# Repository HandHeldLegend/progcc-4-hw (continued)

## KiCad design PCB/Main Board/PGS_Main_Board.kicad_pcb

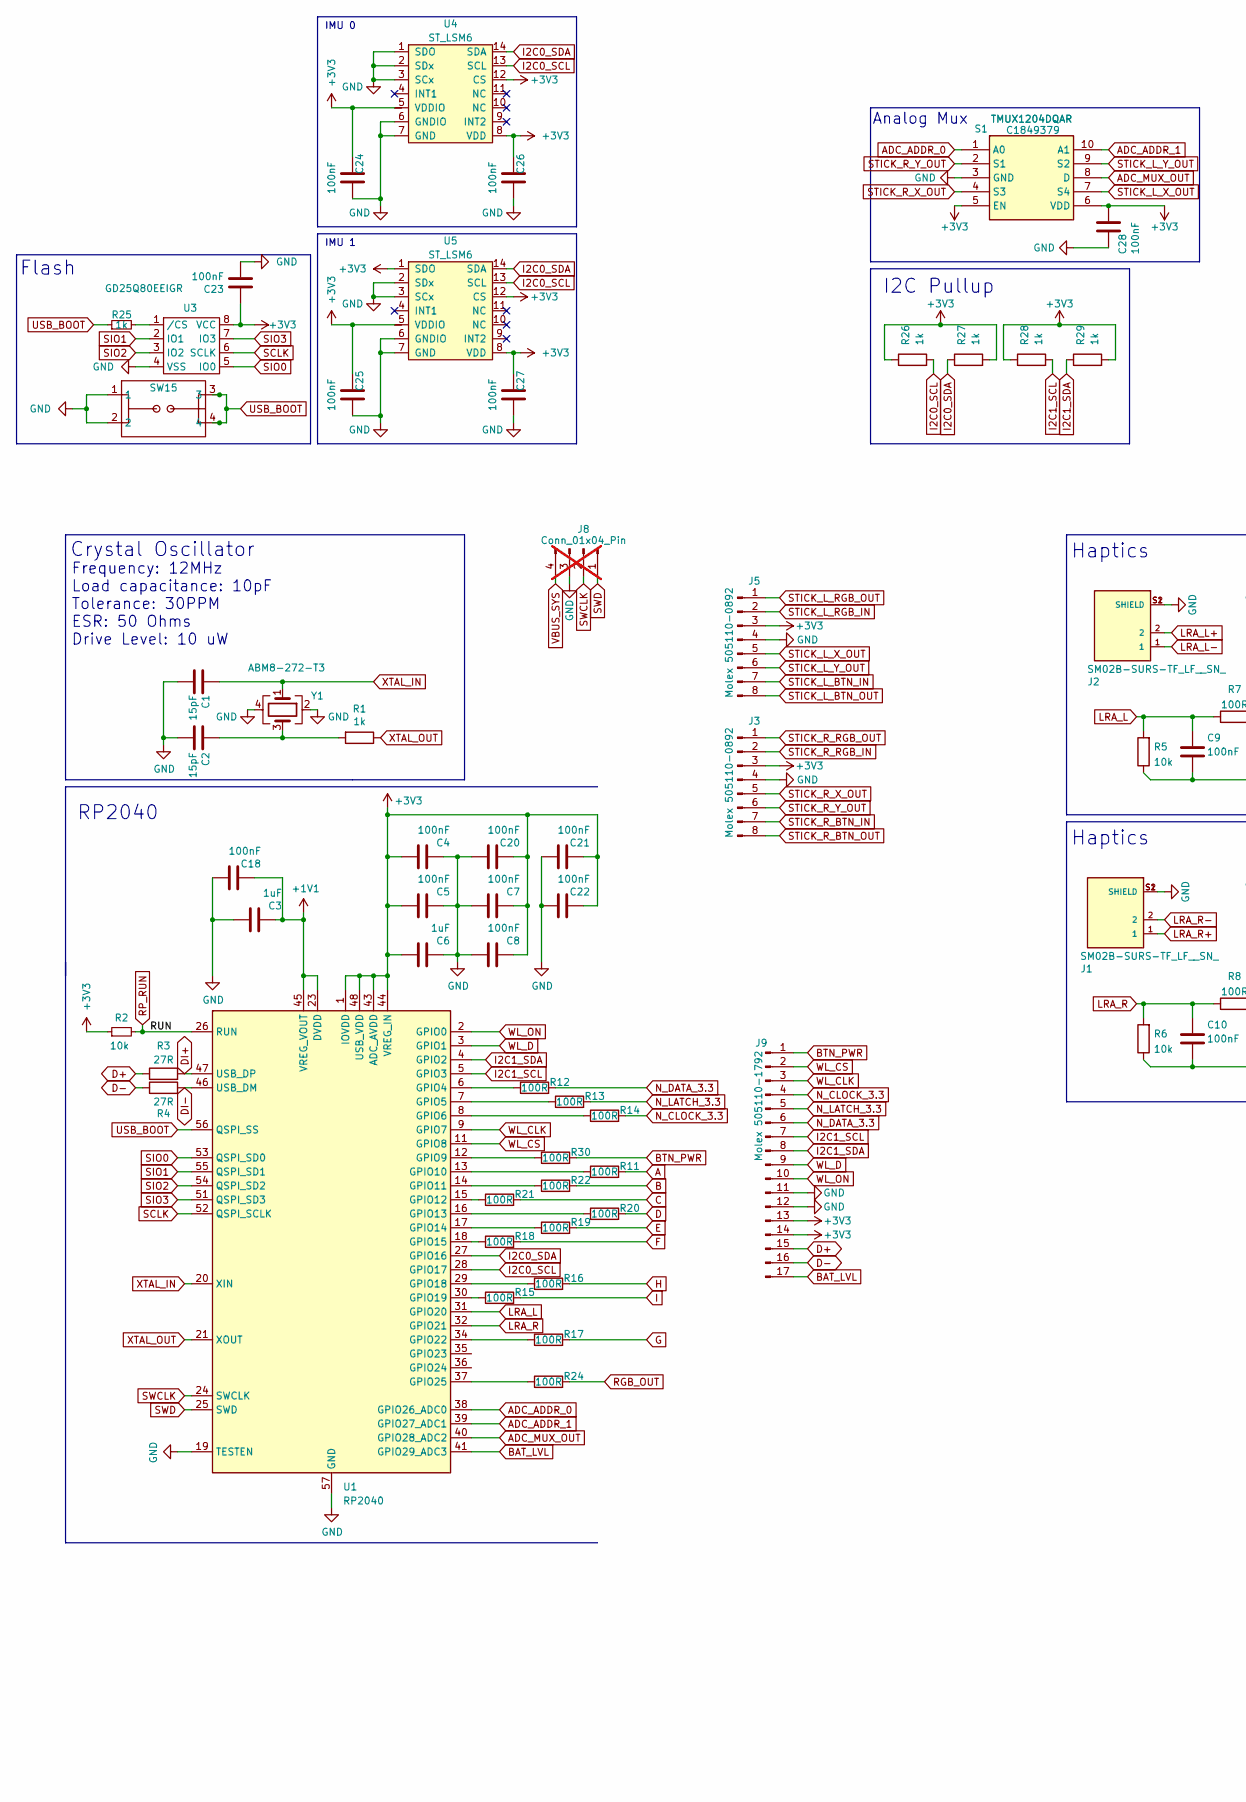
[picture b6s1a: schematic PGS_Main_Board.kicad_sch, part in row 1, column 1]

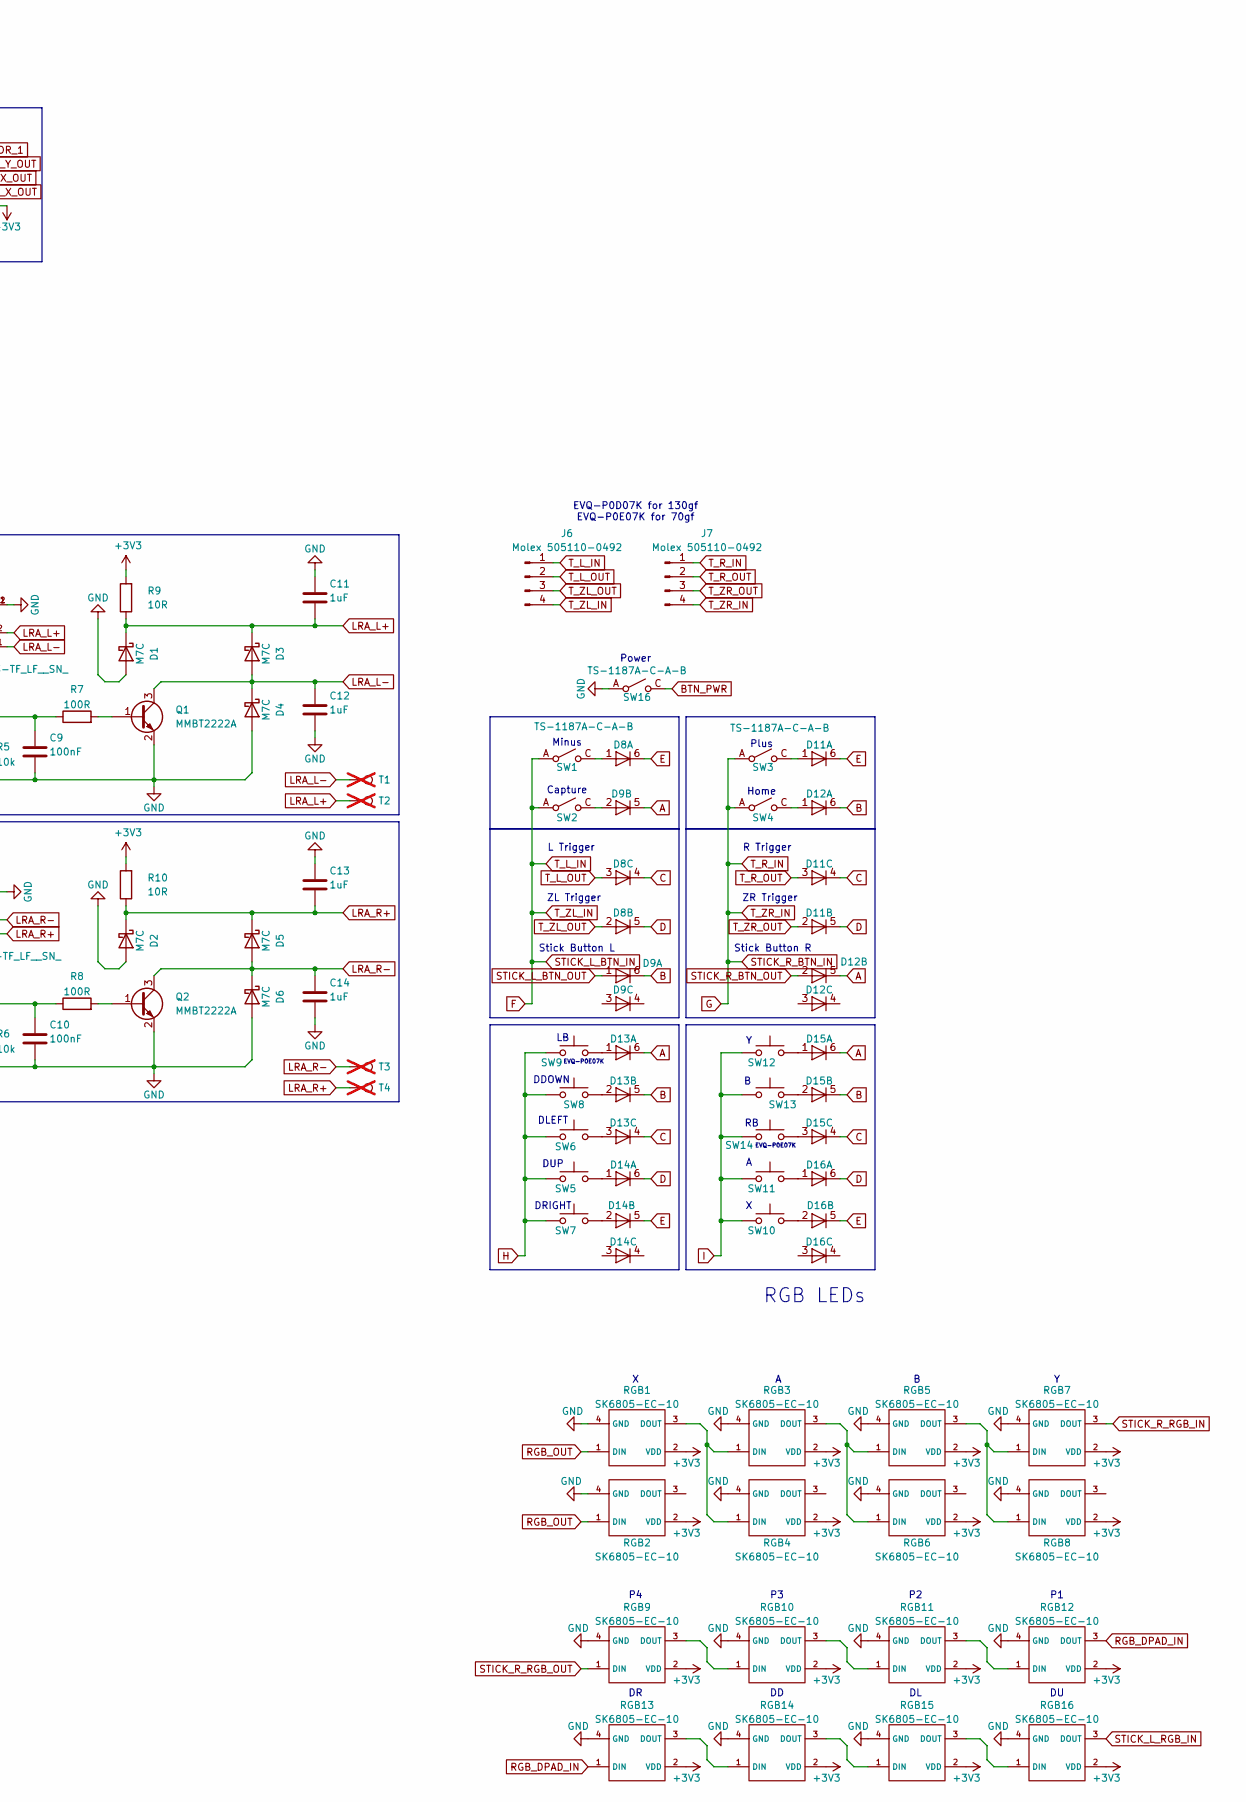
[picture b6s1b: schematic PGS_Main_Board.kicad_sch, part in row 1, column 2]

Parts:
C1, C2: 15pF; C_0402_1005Metric; MPN CC0402FRNPO9BN150; LCSC C326803
C3: 1uF; C_0201_0603Metric; MPN CL03A104KQ3NNNC; LCSC C160831
C4, C5, C7, C8, C9, C10, C18, C20, C21, C22, C23, C24, C25, C26, C27: 100nF; C_0201_0603Metric; MPN CL03A104KQ3NNNC; LCSC C160831
C6, C11, C12, C13, C14: 1uF; C_0201_0603Metric; MPN GRM033R60J105KEA2D; LCSC C76929
C28: 100nF; C_0201_0603Metric; MPN CC0402KRX7R5BB104; LCSC C541406
D1, D2, D3, D4, D5, D6: M7C; D_SOD-523; MPN B5819WT; LCSC C5364321
D8, D9, D11, D12, D13, D14, D15, D16: BAS16VY,115; SOT-363_SC-70-6; MPN BAS16VY,115; LCSC C135826
J1, J2: SM02B-SURS-TF_LF__SN_; JST_SM02B-SURS-TF_LF__SN_; PARTREV N/A; LCSC C566239
J3, J5: Molex 505110-0892; 5051100892; MPN 505110-0892
J6, J7: Molex 505110-0492; 5051100492; MPN 505110-0492
J8: Conn_01x04_Pin; PinHeader_1x04_P2.00mm_Vertical; not fitted
J9: Molex 505110-1792; 5051101792; MPN Molex 505110-1792
Q1, Q2: MMBT2222A; SOT-23; MPN MMBT2222A; LCSC C916372
R1, R25, R26, R27, R28, R29: 1k; R_0201_0603Metric; MPN RC0201FR-071KL; LCSC C138165
R2, R5, R6: 10k; R_0201_0603Metric; MPN RC0201FR-0710KL; LCSC C106225
R3, R4: 27R; R_0201_0603Metric; MPN RC0201FR-0727RL; LCSC C273268
R7, R8: 100R; R_0201_0603Metric; MPN RC0201FR-07100RL; LCSC C77623
R9, R10: 10R; R_0201_0603Metric; MPN RC0201FR-070RL; LCSC C106227
R11, R12, R13, R14, R15, R16, R17, R18, R19, R20, R21, R22, R24, R30: 100R; R_0201_0603Metric; MPN RC0201FR-0727RL; LCSC C273268
RGB1, RGB2, RGB3, RGB4, RGB5, RGB6, RGB7, RGB8, RGB9, RGB10, RGB11, RGB12, RGB13, RGB14, RGB15, RGB16: SK6805-EC-10; MPN SK6805-EC-10
S1: TMUX1204DQAR; Mouser Part Number 595-TMUX1204DQAR
SW1, SW2, SW3, SW4, SW16: TS-1187A-C-A-B; TS-1187A-C-E-B; MPN TS-1187A-C-E-B; LCSC C480267
SW5, SW6, SW7, SW8: SW_Push; pgs_dpad; MPN TC-00100V H5.0 100gf
SW9, SW14: EVQ-P0E07K; EVQP0; MPN EVQ-P0E07K
SW10, SW11, SW12, SW13: SW_Push; pgs_abxy; MPN TC-00100V H5.0 100gf
SW15: 1TS026A-1000-0550; MPN 1TS026A-1000-0550; LCSC C913778
T1, T2, T3, T4: PinHeader_1x01_P1.00mm_Vertical; not fitted
U1: RP2040; QFN-56-1EP_7x7mm_P0.4mm_EP3.2x3.2mm; MPN RP2040; LCSC C2040
U3: GD25Q80EEIGR; USON-8-EP(2x3); MPN GD25Q80EEIGR; LCSC C2874937
U4, U5: ST_LSM6; LGA14; MPN LSM6DSRTR; LCSC C784817
Y1: ABM8-272-T3; Crystal_SMD_3225-4Pin_3.2x2.5mm; MPN ABM8-272-T3; LCSC C20625731

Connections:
+1V1: C3.2, C18.2, U1.23 (DVDD), U1.45 (VREG_VOUT), U1.50 (DVDD)
+3V3: C4.1, C5.1, C6.1, C7.2, C8.2, C20.2, C21.2, C22.2, C23.1, C24.2, C25.2, C26.2, C27.2, C28.1, J3.3, J5.3, J9.13, J9.14, R2.1, R9.2, R10.2, R26.1, R27.2, R28.1, R29.2, RGB1.2 (VDD), RGB2.2 (VDD), RGB3.2 (VDD), RGB4.2 (VDD), RGB5.2 (VDD), RGB6.2 (VDD), RGB7.2 (VDD), RGB8.2 (VDD), RGB9.2 (VDD), RGB10.2 (VDD), RGB11.2 (VDD), RGB12.2 (VDD), RGB13.2 (VDD), RGB14.2 (VDD), RGB15.2 (VDD), RGB16.2 (VDD), S1.5 (EN), S1.6 (VDD), U1.1 (IOVDD), U1.10 (IOVDD), U1.22 (IOVDD), U1.33 (IOVDD), U1.42 (IOVDD), U1.43 (ADC_AVDD), U1.44 (VREG_IN), U1.48 (USB_VDD), U1.49 (IOVDD), U3.8 (VCC), U4.5 (VDDIO), U4.8 (VDD), U4.12 (CS), U5.1 (SDO), U5.5 (VDDIO), U5.8 (VDD), U5.12 (CS)
A: D9.5 (K), D12.5 (K), D13.6 (K), D15.6 (K), R11.2
ADC_ADDR_0: S1.1 (A0), U1.38 (GPIO26_ADC0)
ADC_ADDR_1: S1.10 (A1), U1.39 (GPIO27_ADC1)
ADC_MUX_OUT: S1.8 (D), U1.40 (GPIO28_ADC2)
B: D9.6 (K), D12.6 (K), D13.5 (K), D15.5 (K), R22.2
BAT_LVL: J9.17, U1.41 (GPIO29_ADC3)
BTN_PWR: J9.1, R30.2, SW16.C, SW16.D
C: D8.4 (K), D11.4 (K), D13.4 (K), D15.4 (K), R21.2
D: D8.5 (K), D11.5 (K), D14.6 (K), D16.6 (K), R20.2
D+: J9.15, R3.1
D-: J9.16, R4.1
DI+: R3.2, U1.47 (USB_DP)
DI-: R4.2, U1.46 (USB_DM)
E: D8.6 (K), D11.6 (K), D14.5 (K), D16.5 (K), R19.2
F: J5.7, J6.1, J6.4, R18.2, SW1.A, SW1.B, SW2.A, SW2.B
G: J3.7, J7.1, J7.4, R17.2, SW3.A, SW3.B, SW4.A, SW4.B
GND: C1.2, C2.2, C3.1, C4.2, C5.2, C6.2, C7.1, C8.1, C9.2, C10.2, C11.1, C12.2, C13.1, C14.2, C18.1, C20.1, C21.1, C22.1, C23.2, C24.1, C25.1, C26.1, C27.1, C28.2, D1.2 (A), D2.2 (A), D4.2 (A), D6.2 (A), J1.S1 (SHIELD), J1.S2 (SHIELD), J2.S1 (SHIELD), J2.S2 (SHIELD), J3.4, J5.4, J8.3, J9.11, J9.12, Q1.2 (E), Q2.2 (E), R5.1, R6.1, RGB1.4 (GND), RGB2.4 (GND), RGB3.4 (GND), RGB4.4 (GND), RGB5.4 (GND), RGB6.4 (GND), RGB7.4 (GND), RGB8.4 (GND), RGB9.4 (GND), RGB10.4 (GND), RGB11.4 (GND), RGB12.4 (GND), RGB13.4 (GND), RGB14.4 (GND), RGB15.4 (GND), RGB16.4 (GND), S1.3 (GND), SW15.1, SW15.2, SW16.A, SW16.B, U1.19 (TESTEN), U1.57 (GND), U3.4 (VSS), U4.1 (SDO), U4.2 (SDx), U4.3 (SCx), U4.6 (GNDIO), U4.7 (GND), U5.2 (SDx), U5.3 (SCx), U5.6 (GNDIO), U5.7 (GND), Y1.2, Y1.4
H: R16.2, SW5.1, SW6.1, SW7.1, SW8.1, SW9.1
I: R15.2, SW10.1, SW11.1, SW12.1, SW13.1, SW14.1
I2C0_SCL: R26.2, U1.28 (GPIO17), U4.13 (SCL), U5.13 (SCL)
I2C0_SDA: R27.1, U1.27 (GPIO16), U4.14 (SDA), U5.14 (SDA)
I2C1_SCL: J9.7, R28.2, U1.5 (GPIO3)
I2C1_SDA: J9.8, R29.1, U1.4 (GPIO2)
LRA_L: C9.1, R5.2, R7.1, U1.31 (GPIO20)
LRA_L+: C11.2, D1.1 (K), D3.1 (K), J2.2, R9.1, T2.1
LRA_L-: C12.1, D3.2 (A), D4.1 (K), J2.1, Q1.3 (C), T1.1
LRA_R: C10.1, R6.2, R8.1, U1.32 (GPIO21)
LRA_R+: C13.2, D2.1 (K), D5.1 (K), J1.1, R10.1, T4.1
LRA_R-: C14.1, D5.2 (A), D6.1 (K), J1.2, Q2.3 (C), T3.1
N_CLOCK_3.3: J9.4, R14.2
N_DATA_3.3: J9.6, R12.2
N_LATCH_3.3: J9.5, R13.2
unnamed: C2.1, R1.2, Y1.3
unnamed: D8.1 (A), SW1.C, SW1.D
unnamed: D9.2 (A), SW2.C, SW2.D
unnamed: D11.1 (A), SW3.C, SW3.D
unnamed: D12.1 (A), SW4.C, SW4.D
unnamed: D13.1 (A), SW9.2
unnamed: D13.2 (A), SW8.2
unnamed: D13.3 (A), SW6.2
unnamed: D14.1 (A), SW5.2
unnamed: D14.2 (A), SW7.2
unnamed: D15.1 (A), SW12.2
unnamed: D15.2 (A), SW13.2
unnamed: D15.3 (A), SW14.2
unnamed: D16.1 (A), SW11.2
unnamed: D16.2 (A), SW10.2
unnamed: Q1.1 (B), R7.2
unnamed: Q2.1 (B), R8.2
unnamed: RGB1.3 (DOUT), RGB3.1 (DIN), RGB4.1 (DIN)
unnamed: RGB3.3 (DOUT), RGB5.1 (DIN), RGB6.1 (DIN)
unnamed: RGB5.3 (DOUT), RGB7.1 (DIN), RGB8.1 (DIN)
unnamed: RGB9.3 (DOUT), RGB10.1 (DIN)
unnamed: RGB10.3 (DOUT), RGB11.1 (DIN)
unnamed: RGB11.3 (DOUT), RGB12.1 (DIN)
unnamed: RGB13.3 (DOUT), RGB14.1 (DIN)
unnamed: RGB14.3 (DOUT), RGB15.1 (DIN)
unnamed: RGB15.3 (DOUT), RGB16.1 (DIN)
unnamed: R12.1, U1.6 (GPIO4)
unnamed: R13.1, U1.7 (GPIO5)
unnamed: R14.1, U1.8 (GPIO6)
unnamed: R30.1, U1.12 (GPIO9)
unnamed: R11.1, U1.13 (GPIO10)
unnamed: R22.1, U1.14 (GPIO11)
unnamed: R21.1, U1.15 (GPIO12)
unnamed: R20.1, U1.16 (GPIO13)
unnamed: R19.1, U1.17 (GPIO14)
unnamed: R18.1, U1.18 (GPIO15)
unnamed: R16.1, U1.29 (GPIO18)
unnamed: R15.1, U1.30 (GPIO19)
unnamed: R17.1, U1.34 (GPIO22)
unnamed: R24.1, U1.37 (GPIO25)
unnamed: R25.2, U3.1 (/CS)
RGB_DPAD_IN: RGB12.3 (DOUT), RGB13.1 (DIN)
RGB_OUT: R24.2, RGB1.1 (DIN), RGB2.1 (DIN)
RP_RUN: R2.2, U1.26 (RUN)
SCLK: U1.52 (QSPI_SCLK), U3.6 (SCLK)
SIO0: U1.53 (QSPI_SD0), U3.5 (IO0)
SIO1: U1.55 (QSPI_SD1), U3.2 (IO1)
SIO2: U1.54 (QSPI_SD2), U3.3 (IO2)
SIO3: U1.51 (QSPI_SD3), U3.7 (IO3)
STICK_L_BTN_OUT: D9.1 (A), J5.8
STICK_L_RGB_IN: J5.2, RGB16.3 (DOUT)
STICK_L_RGB_OUT: J5.1
STICK_L_X_OUT: J5.5, S1.7 (S4)
STICK_L_Y_OUT: J5.6, S1.9 (S2)
STICK_R_BTN_OUT: D12.2 (A), J3.8
STICK_R_RGB_IN: J3.2, RGB7.3 (DOUT)
STICK_R_RGB_OUT: J3.1, RGB9.1 (DIN)
STICK_R_X_OUT: J3.5, S1.4 (S3)
STICK_R_Y_OUT: J3.6, S1.2 (S1)
SWCLK: J8.2, U1.24 (SWCLK)
SWD: J8.1, U1.25 (SWD)
T_L_OUT: D8.3 (A), J6.2
T_R_OUT: D11.3 (A), J7.2
T_ZL_OUT: D8.2 (A), J6.3
T_ZR_OUT: D11.2 (A), J7.3
USB_BOOT: R25.1, SW15.3, SW15.4, U1.56 (QSPI_SS)
VBUS_SYS: J8.4
WL_CLK: J9.3, U1.9 (GPIO7)
WL_CS: J9.2, U1.11 (GPIO8)
WL_D: J9.9, U1.3 (GPIO1)
WL_ON: J9.10, U1.2 (GPIO0)
XTAL_IN: C1.1, U1.20 (XIN), Y1.1
XTAL_OUT: R1.1, U1.21 (XOUT)

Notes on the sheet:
R Trigger
Stick Button R
Power
EVQ-P0E07K
Analog Mux
RP2040
Haptics
RGB LEDs
DDOWN
Crystal Oscillator
EVQ-P0D07K for 130gf EVQ-P0E07K for 70gf
DRIGHT
IMU 1
Flash
ZR Trigger
DUP
IMU 0
Plus
ZL Trigger
DLEFT
Stick Button L
I2C Pullup
Frequency: 12MHz Load capacitance: 10pF Tolerance: 30PPM ESR: 50 Ohms Drive Level: 10 uW
Minus
Capture
Home
L Trigger

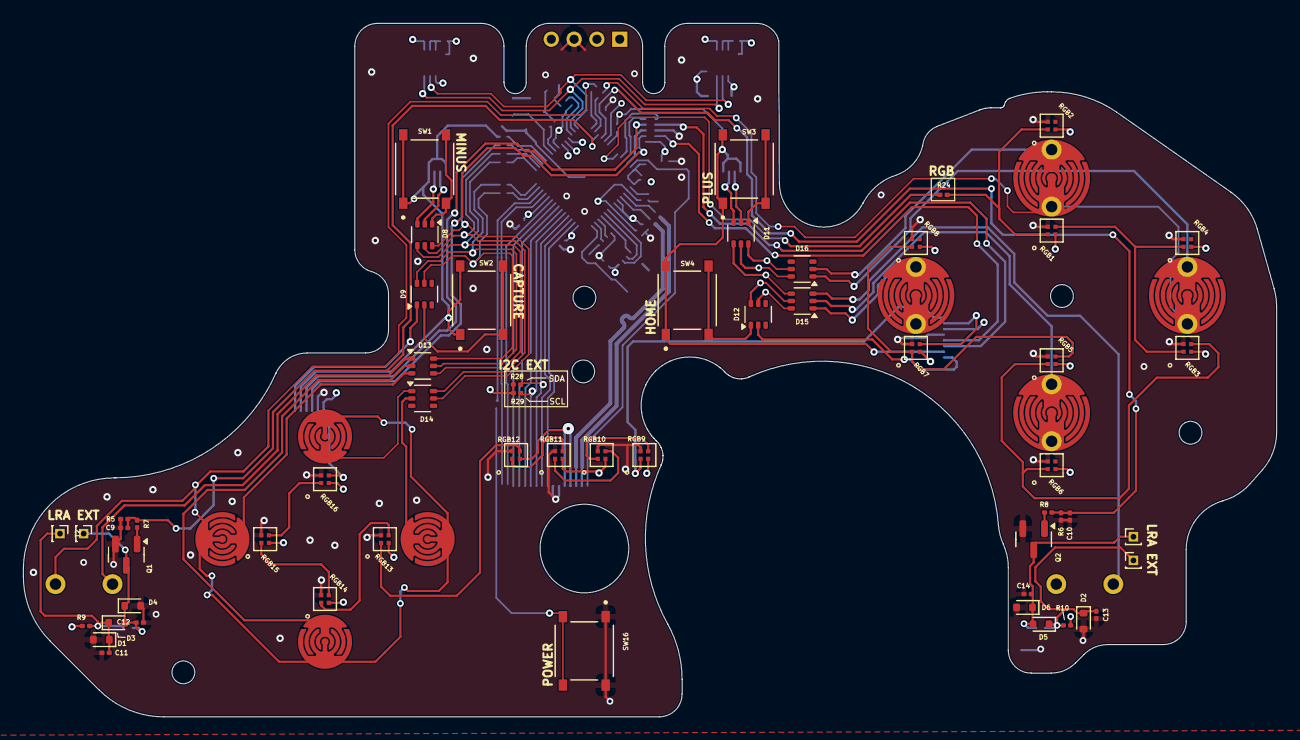
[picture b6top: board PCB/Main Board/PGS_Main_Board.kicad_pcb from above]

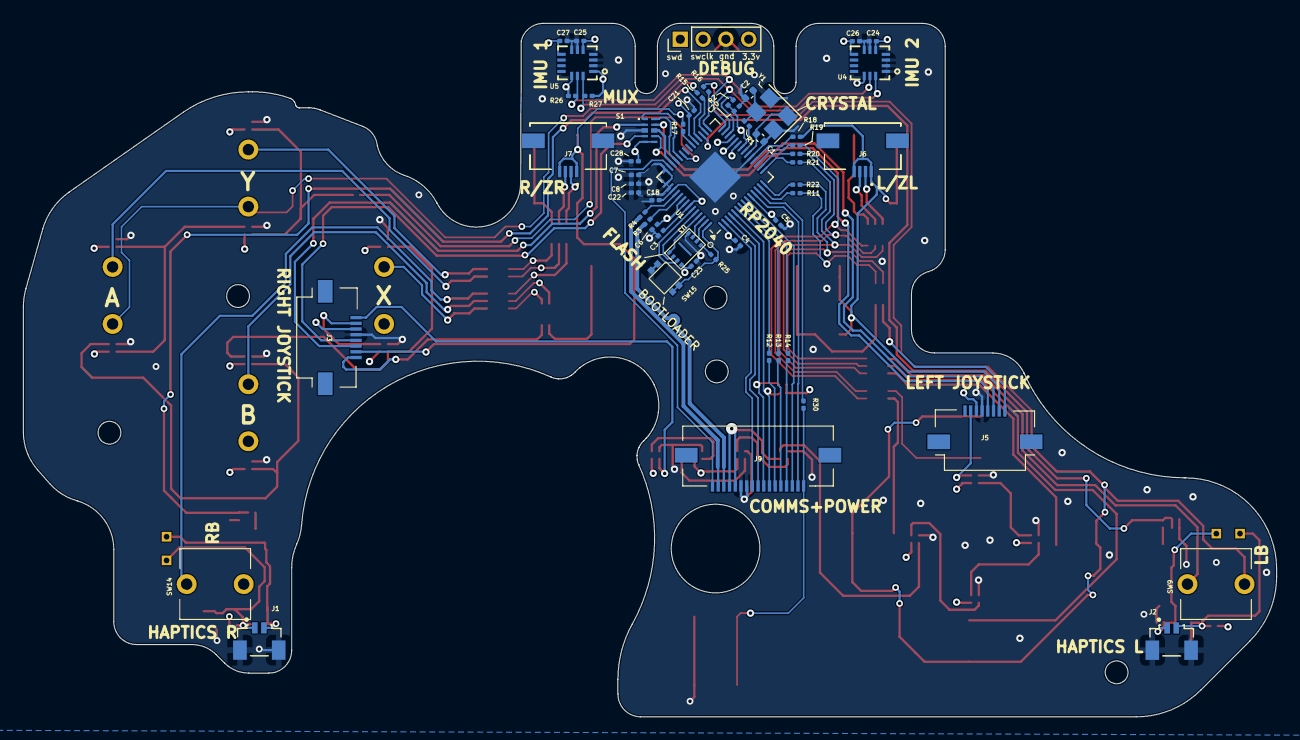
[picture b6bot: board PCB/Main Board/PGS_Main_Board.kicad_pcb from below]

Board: 4 copper layers, 109.9 x 60.8 mm, 119 parts (55 on the bottom side), 105 nets.

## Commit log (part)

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2025-05-15 Initial progress commit
2025-05-16 PCB Routing
2025-05-16 Routing update
2025-05-16 More Routing
2025-05-16 Routing/Labelling
2025-05-17 Board Pos Fixes
    - Fix RGB Resistor position
    - Move input matrix diode arrays
    - Move conflicting LRA driver components
2025-05-18 More Routing
    - Stick Module Done
    - BT Comms + Power Done
2025-05-18 Final Routing 3D Export
    - Export 3D STEP models
2025-05-18 Board Fixes
    - Relocate RGB on main board to align with pass-through holes
    - Exchange battery connector for through-hole battery JST connector and change pcb shape
    - New interactive BOM with PCB previews
2025-05-19 Add and Organize 3D Files
2025-05-19 Reorganize files
2025-05-19 Update Date
2025-05-19 Fix Shell Tolerance
2025-05-20 Add locating holes
    Middle shell locating holes for threaded inserts
2025-05-20 Fixes to top shell
    - Top shell was off center Y axis
    - Fixed up top shell
    - Fixed other out of alignment items
2025-05-20 Add Standoffs
    - Add posts for main PCB support from mid shell
2025-05-20 Add 2 screws to master file
2025-05-20 Button Cutouts
    Change opening to 0.18mm on top shell for ABXY
    0.20 for DPad
2025-05-20 PCB Zip file
2025-05-20 Tolerance Updates
    M3 screws have a 4.25mm offset for all shell parts
    Plastic screw holes all normalized to 1.65mm for better fitment
2025-07-08 Update gitignore
2025-07-11 Update Trigger Module
2025-07-20 Main Board Update
    - Put 1uF caps closer to designated pins
    - Update timestamp on PCB mask
2025-07-21 Annotate schematic
    1uF capacitor annotation updated for main PCB
2025-08-04 Membrane Thickness increase
    - Silicone membrane actuator thickness increased from 0.15mm -> 0.4mm
2025-08-19 CAD Updates
    - ABXY Button updated to have unique heights per-button to match the shell profile.
2025-09-02 USBW Update
    - Implement fuel gauge IC
2025-09-02 Change font for plus symbol
2025-09-23 Main Board/Trigger Board Update
    - Main board updated with Kailh tactile switches
    - Trigger board updated with Kailh tactile switches
    - USBW board updated to remove unneeded diode, move position of USB-C port
2025-09-23 USB C Port Adjustment
    - Spacing between USB C port and USB C cable adjusted
2025-09-24 USB-C Adjustment
    Adjusted USB-C port to have 0.3mm clearance between shell and overmold on the USB-C cable
2025-09-29 CAD Updates
    - Trigger updates
    - Rear grip updates
    - Gateplate updates
    - Shell Updates
2025-10-09 Grip button adjustments
    - Make custom silicone pad
2025-10-16 Update joystick
    Increase depth of shaft female portion by 0.2mm
